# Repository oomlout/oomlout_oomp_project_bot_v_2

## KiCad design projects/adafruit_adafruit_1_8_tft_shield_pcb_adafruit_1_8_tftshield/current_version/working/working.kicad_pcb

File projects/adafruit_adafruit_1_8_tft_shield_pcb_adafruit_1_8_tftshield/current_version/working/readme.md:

# adafruit_1_8_tft_shield_pcb
 
## summary 
* id: adafruit_adafruit_1_8_tft_shield_pcb_adafruit_1_8_tftshield
* user: adafruit
* name: adafruit_1_8_tft_shield_pcb
* board: adafruit_1_8_tftshield
* repo: https://github.com/adafruit/Adafruit-1.8-TFT-Shield-PCB

* src_file_repo_sch: 
* src_file_repo_sch_link: https://github.com/adafruit/Adafruit-1.8-TFT-Shield-PCB/tree/master/
* full details link: https://github.com/oomlout/oomlout_oomp_project_bot_v_2/tree/main/projects/adafruit_adafruit_1_8_tft_shield_pcb_adafruit_1_8_tftshield/current_version/working  

## schematic  
  
[schematic (pdf)](working_schematic.pdf) 

## pcb  

[board (pdf)](working.pdf)  

## working_bom
| Id | Designator | Footprint | Quantity | Designation | Supplier and ref |  | None | 
| --- | --- | --- | --- | --- | --- | --- | --- | 
| 1 | C1,C2 | 0805-NO | 2 | 10uF |  |  | [''] | 
| 2 | DIGITALS1,DIGITALS0 | 1X08_ROUND | 2 |  |  |  | [''] | 
| 3 | Q2 | SOT23-WIDE | 1 | BSS138 |  |  | [''] | 
| 4 | BTN3,RESET0,BTN1,BTN2 | EVQ-Q2_SMALLER | 4 | EVQQ |  |  | [''] | 
| 5 | R9,R2 | 0805-NO | 2 | 10K |  |  | [''] | 
| 6 | U$1 | JD-T1800 | 1 | DISP_LCD_JDT1800 |  |  | [''] | 
| 7 | U$3 | MICROSD | 1 | MICROSD |  |  | [''] | 
| 8 | M1 | ARDUINOR3_ICSP | 1 | ARDUINO_R3_ICSP |  |  | [''] | 
| 9 | U$9 | PCBFEAT-REV-040 | 1 |  |  |  | [''] | 
| 10 | IC1 | QFN24_4MM | 1 | ATSAMD09D14A-MU |  |  | [''] | 
| 11 | JP1 | 1X10_ROUND | 1 |  |  |  | [''] | 
| 12 | IC2 | SOT23-5L | 1 | AP2112K-3.3 |  |  | [''] | 
| 13 | ANALOGS0 | 1X06_ROUND | 1 |  |  |  | [''] | 
| 14 | C3,C4 | 0805-NO | 2 | 0.1uF |  |  | [''] | 
| 15 | R8 | RESPACK_4X0603_NO | 1 | 10K |  |  | [''] | 
| 16 | FID1,FID3 | FIDUCIAL_1MM | 2 | FIDUCIAL_1MM |  |  | [''] | 
| 17 | Q3 | SOT363 | 1 | BSS138 |  |  | [''] | 
| 18 | U1 | TSSOP16 | 1 | 74HC4050 |  |  | [''] | 
| 19 | U$7 | ADAFRUIT_5MM | 1 |  |  |  | [''] | 
| 20 | SW1 | SKQUBAE010 | 1 | NAVSWITCHSKQUABAUE010 |  |  | [''] | 
| 21 | R5 | 0805-NO | 1 | 1K |  |  | [''] | 
| 22 | R1 | 0805-NO | 1 | 22 ohm |  |  | [''] | 
| 23 | AD0,AD1 | SOLDERJUMPER_ARROW_NOPASTE | 2 |  |  |  | [''] | 
| 24 | TP2,TP1 | TESTPOINT_ROUND_2MM | 2 |  |  |  | [''] | 
| 25 | U$5 | ADAFRUIT_TEXT_30MM | 1 |  |  |  | [''] | 
| 26 | U$8 | SEESAW_LOGO | 1 |  |  |  | [''] | 

## bom_schematic
| Ref | Qnty | Value | Cmp name | Footprint | Description | Vendor | DNP | 
| --- | --- | --- | --- | --- | --- | --- | --- | 
| AD0, AD1 | 2 | SOLDERJUMPER | SOLDERJUMPER | working:SOLDERJUMPER_ARROW_NOPASTE |  |  |  | 
| ANALOGS0 | 1 | HEADER-1X6ROUND | HEADER-1X6ROUND | working:1X06_ROUND |  |  |  | 
| BTN1, BTN2, BTN3 | 3 | EVQQ | SWITCH_TACT_SMT_EVQQ2_SMALL | working:EVQ-Q2_SMALLER |  |  |  | 
| C1, C2 | 2 | 10uF | CAP_CERAMIC0805-NOOUTLINE | working:0805-NO |  |  |  | 
| C3, C4 | 2 | 0.1uF | CAP_CERAMIC0805-NOOUTLINE | working:0805-NO |  |  |  | 
| DIGITALS0, DIGITALS1 | 2 | HEADER-1X8ROUND | HEADER-1X8ROUND | working:1X08_ROUND |  |  |  | 
| FID1, FID3 | 2 | FIDUCIAL_1MM | FIDUCIAL_1MM | working:FIDUCIAL_1MM |  |  |  | 
| IC1 | 1 | ATSAMD09D14A-MU | ATSAMD09D14A-MU | working:QFN24_4MM |  |  |  | 
| IC2 | 1 | LP298XS | LP298XS | working:SOT23-5L |  |  |  | 
| JP1 | 1 | HEADER-1X10ROUND | HEADER-1X10ROUND | working:1X10_ROUND |  |  |  | 
| M1 | 1 | ARDUINO_R3_ICSP | ARDUINO_R3_ICSP | working:ARDUINOR3_ICSP |  |  |  | 
| Q2 | 1 | BSS138 | MOSFET-NWIDE | working:SOT23-WIDE |  |  |  | 
| Q3 | 1 | BSS138 | MOSFET-N_DUAL | working:SOT363 |  |  |  | 
| R1 | 1 | 22 ohm | RESISTOR0805_NOOUTLINE | working:0805-NO |  |  |  | 
| R2, R9 | 2 | 10K | RESISTOR0805_NOOUTLINE | working:0805-NO |  |  |  | 
| R5 | 1 | 1K | RESISTOR0805_NOOUTLINE | working:0805-NO |  |  |  | 
| R8 | 1 | 10K | RESISTOR_4PACK_NO | working:RESPACK_4X0603_NO |  |  |  | 
| RESET0 | 1 | EVQQ | SWITCH_TACT_SMT_EVQQ2_SMALL | working:EVQ-Q2_SMALLER |  |  |  | 
| SW1 | 1 | NAVSWITCHSKQUABAUE010 | NAVSWITCHSKQUABAUE010 | working:SKQUBAE010 |  |  |  | 
| TP1, TP2 | 2 | TESTPOINTROUND2MM | TESTPOINTROUND2MM | working:TESTPOINT_ROUND_2MM |  |  |  | 
| U1 | 1 | 74HC4050 | 74HC4050DTSSOP | working:TSSOP16 |  |  |  | 
| U$1 | 1 | DISP_LCD_JDT1800 | DISP_LCD_JDT1800 | working:JD-T1800 |  |  |  | 
| U$3 | 1 | MICROSD | MICROSD | working:MICROSD |  |  |  |

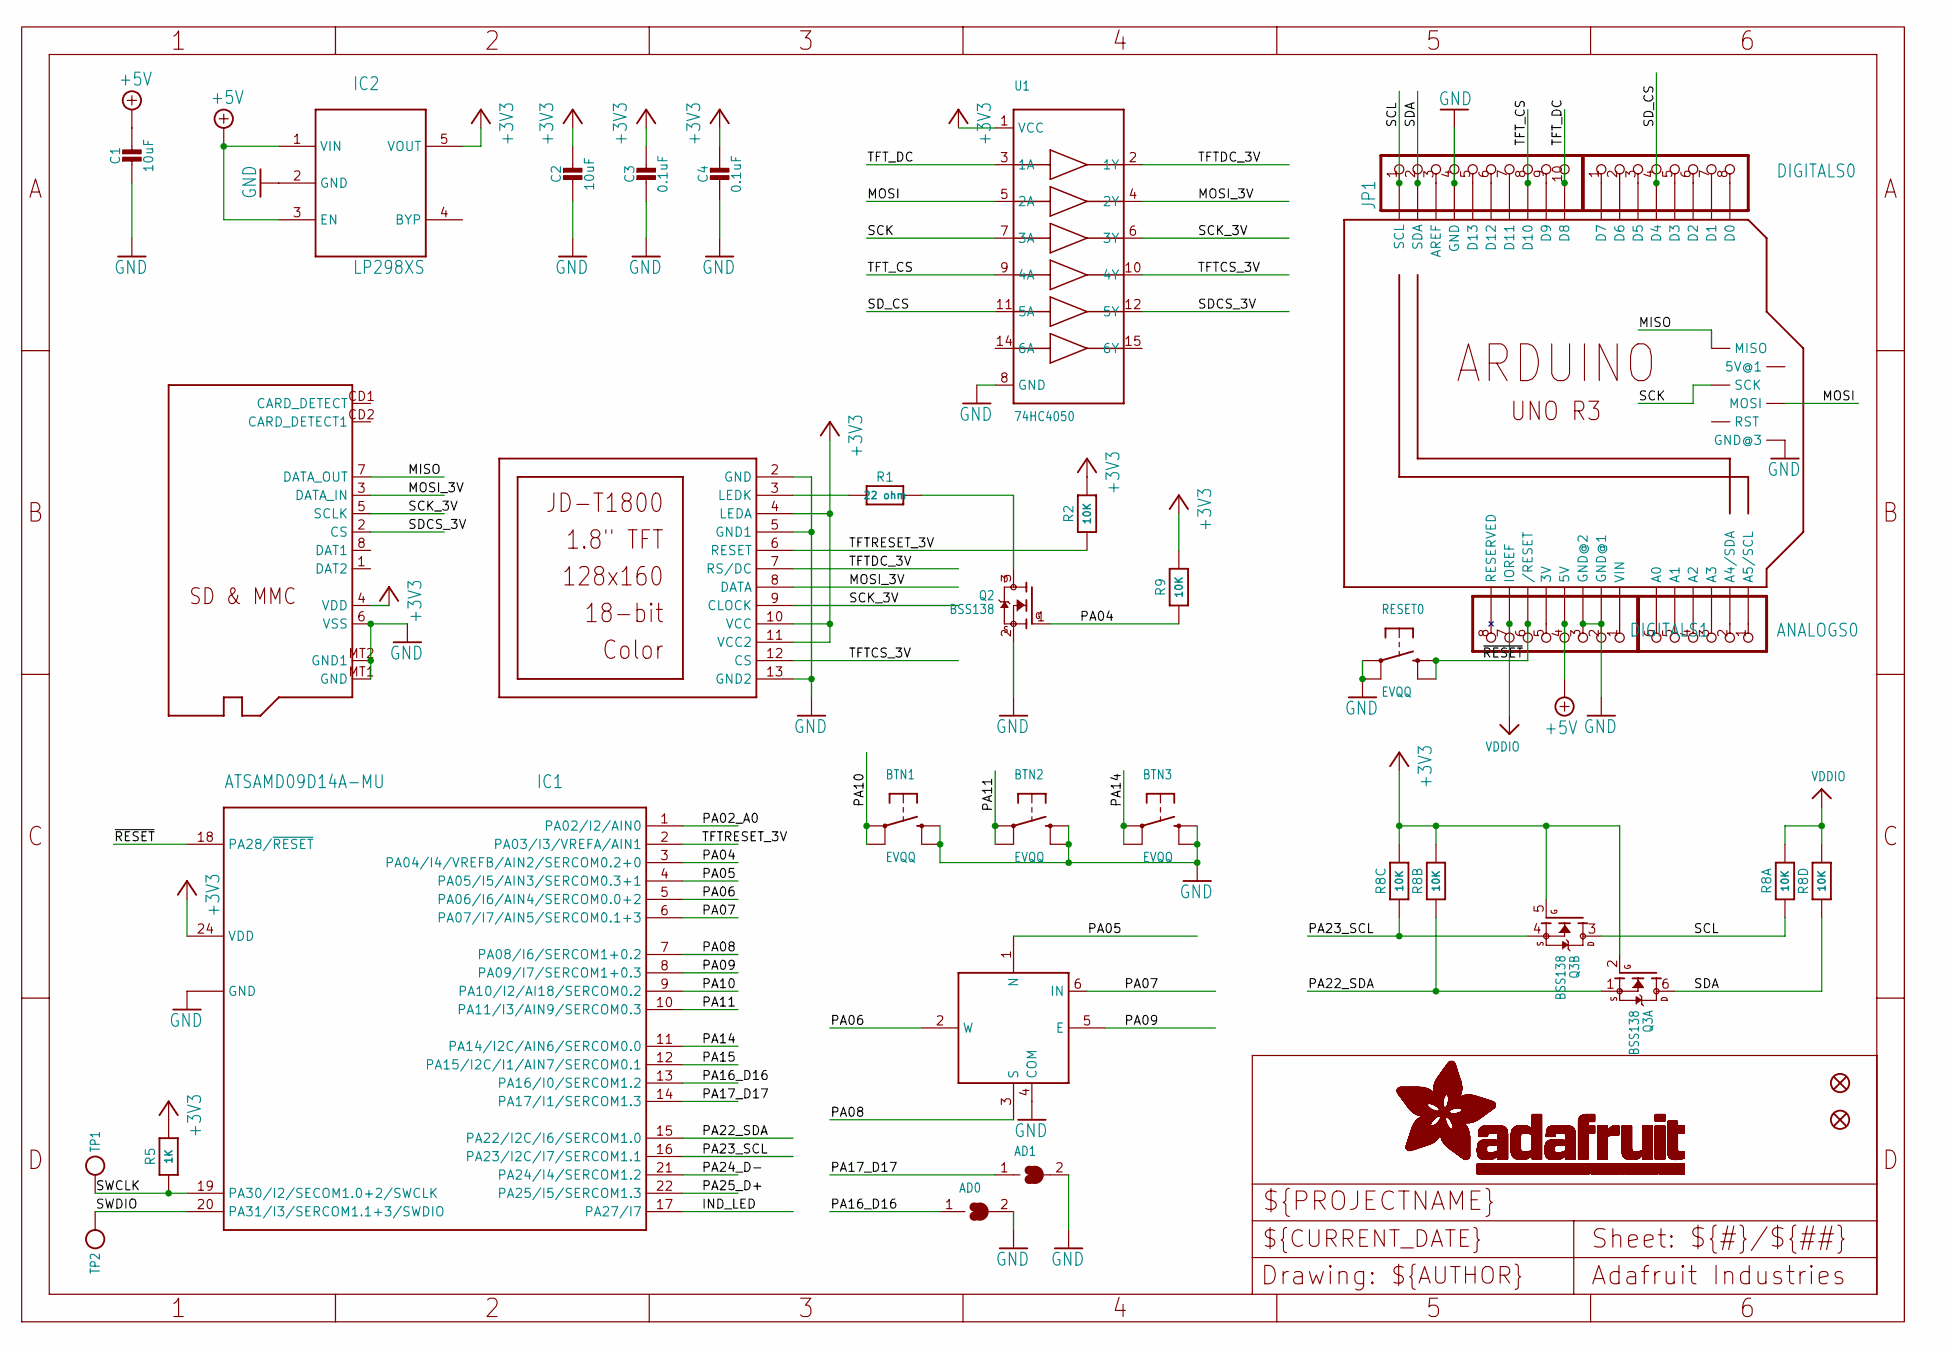
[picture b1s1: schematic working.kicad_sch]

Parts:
AD0, AD1: SOLDERJUMPER; SOLDERJUMPER_ARROW_NOPASTE
ANALOGS0: HEADER-1X6ROUND; 1X06_ROUND
BTN1, BTN2, BTN3: EVQQ; EVQ-Q2_SMALLER
C1, C2: 10uF; 0805-NO
C3, C4: 0.1uF; 0805-NO
DIGITALS0, DIGITALS1: HEADER-1X8ROUND; 1X08_ROUND
FID1, FID3: FIDUCIAL_1MM
IC1: ATSAMD09D14A-MU; QFN24_4MM
IC2: LP298XS; SOT23-5L
JP1: HEADER-1X10ROUND; 1X10_ROUND
M1: ARDUINO_R3_ICSP; ARDUINOR3_ICSP
Q2: BSS138; SOT23-WIDE
Q3: BSS138; SOT363
R1: 22 ohm; 0805-NO
R2, R9: 10K; 0805-NO
R5: 1K; 0805-NO
R8: 10K; RESPACK_4X0603_NO
RESET0: EVQQ; EVQ-Q2_SMALLER
SW1: NAVSWITCHSKQUABAUE010; SKQUBAE010
TP1, TP2: TESTPOINTROUND2MM; TESTPOINT_ROUND_2MM
U1: 74HC4050; TSSOP16
U$1: DISP_LCD_JDT1800; JD-T1800
U$3: MICROSD

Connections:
+3.3V: DIGITALS1.5, M1.3V
+3V3: C2.1, C3.1, C4.1, IC1.24 (VDD), IC2.5 (VOUT), Q3.2 (G), Q3.5 (G), R2.2, R5.2, R8.6 (2), R8.7 (2), R9.2, U1.1 (VCC), U$1.4 (LEDA), U$1.10 (VCC), U$1.11 (VCC2), U$3.4 (VDD)
+5V: C1.1, DIGITALS1.4, IC2.1 (VIN), IC2.3 (EN), M1.5V
A0: ANALOGS0.6, M1.A0
A1: ANALOGS0.5, M1.A1
A2: ANALOGS0.4, M1.A2
A4: ANALOGS0.2, M1.A4 (A4/SDA)
A5: ANALOGS0.1, M1.A5 (A5/SCL)
AREF: JP1.3, M1.AREF
D0: DIGITALS0.8, M1.D0
D1: DIGITALS0.7, M1.D1
D2: DIGITALS0.6, M1.D2
D3: DIGITALS0.5, M1.D3
D5: DIGITALS0.3, M1.D5
D6: DIGITALS0.2, M1.D6
D7: DIGITALS0.1, M1.D7
D9: JP1.9, M1.D9
GND: AD0.2, AD1.2, BTN1.B (S), BTN1.B' (S1), BTN2.B (S), BTN2.B' (S1), BTN3.B (S), BTN3.B' (S1), C1.2, C2.2, C3.2, C4.2, DIGITALS1.2, DIGITALS1.3, IC1.23 (GND), IC1.THERM (GND), IC2.2 (GND), JP1.4, M1.GND, M1.GND@1 (GND@2), M1.GND@2 (GND@3), M1.GND@3 (GND@1), Q2.2 (S), RESET0.A, RESET0.A' (P1), SW1.4 (COM), U1.8 (GND), U$1.2 (GND), U$1.5 (GND1), U$1.13 (GND2), U$3.6 (VSS), U$3.MT1 (GND), U$3.MT2 (GND1)
IND_LED: IC1.17 (PA27/I7)
MISO: M1.MISO, U$3.7 (DATA_OUT)
MOSI: M1.MOSI, U1.5 (2A)
MOSI_3V: U1.4 (2Y), U$1.8 (DATA), U$3.3 (DATA_IN)
unnamed: R1.1, U$1.3 (LEDK)
unnamed: Q2.3 (D), R1.2
unnamed: JP1.5, M1.D13
unnamed: JP1.6, M1.D12
unnamed: JP1.7, M1.D11
unnamed: ANALOGS0.3, M1.A3
unnamed: DIGITALS1.8, M1.RESERVED
PA02_A0: IC1.1 (PA02/I2/AIN0)
PA04: IC1.3 (PA04/I4/VREFB/AIN2/SERCOM0.2+0), Q2.1 (G), R9.1
PA05: IC1.4 (PA05/I5/AIN3/SERCOM0.3+1), SW1.1 (N)
PA06: IC1.5 (PA06/I6/AIN4/SERCOM0.0+2), SW1.2 (W)
PA07: IC1.6 (PA07/I7/AIN5/SERCOM0.1+3), SW1.6 (IN)
PA08: IC1.7 (PA08/I6/SERCOM1+0.2), SW1.3 (S)
PA09: IC1.8 (PA09/I7/SERCOM1+0.3), SW1.5 (E)
PA10: BTN1.A, BTN1.A' (P1), IC1.9 (PA10/I2/AI18/SERCOM0.2)
PA11: BTN2.A, BTN2.A' (P1), IC1.10 (PA11/I3/AIN9/SERCOM0.3)
PA14: BTN3.A, BTN3.A' (P1), IC1.11 (PA14/I2C/AIN6/SERCOM0.0)
PA15: IC1.12 (PA15/I2C/I1/AIN7/SERCOM0.1)
PA16_D16: AD0.1, IC1.13 (PA16/I0/SERCOM1.2)
PA17_D17: AD1.1, IC1.14 (PA17/I1/SERCOM1.3)
PA22_SDA: IC1.15 (PA22/I2C/I6/SERCOM1.0), Q3.1 (S), R8.2 (1)
PA23_SCL: IC1.16 (PA23/I2C/I7/SERCOM1.1), Q3.4 (S), R8.3 (1)
PA24_D-: IC1.21 (PA24/I4/SERCOM1.2)
PA25_D+: IC1.22 (PA25/I5/SERCOM1.3)
SCK: M1.SCK, U1.7 (3A)
SCK_3V: U1.6 (3Y), U$1.9 (CLOCK), U$3.5 (SCLK)
SCL: JP1.1, M1.SCL, Q3.3 (D), R8.1
SDA: JP1.2, M1.SDA, Q3.6 (D), R8.4 (1)
SDCS_3V: U1.12 (5Y), U$3.2 (CS)
SD_CS: DIGITALS0.4, M1.D4, U1.11 (5A)
SWCLK: IC1.19 (PA30/I2/SECOM1.0+2/SWCLK), R5.1, TP1.P$1
SWDIO: IC1.20 (PA31/I3/SERCOM1.1+3/SWDIO), TP2.P$1
TFTCS_3V: U1.10 (4Y), U$1.12 (CS)
TFTDC_3V: U1.2 (1Y), U$1.7 (RS/DC)
TFTRESET_3V: IC1.2 (PA03/I3/VREFA/AIN1), R2.1, U$1.6 (RESET)
TFT_CS: JP1.8, M1.D10, U1.9 (4A)
TFT_DC: JP1.10, M1.D8, U1.3 (1A)
VDDIO: DIGITALS1.7, M1.IOREF, R8.5 (2), R8.8 (2)
VIN: DIGITALS1.1, M1.VIN
~RESET: DIGITALS1.6, IC1.18 (PA28/~RESET), M1.RESET (/RESET), RESET0.B (S), RESET0.B' (S1)

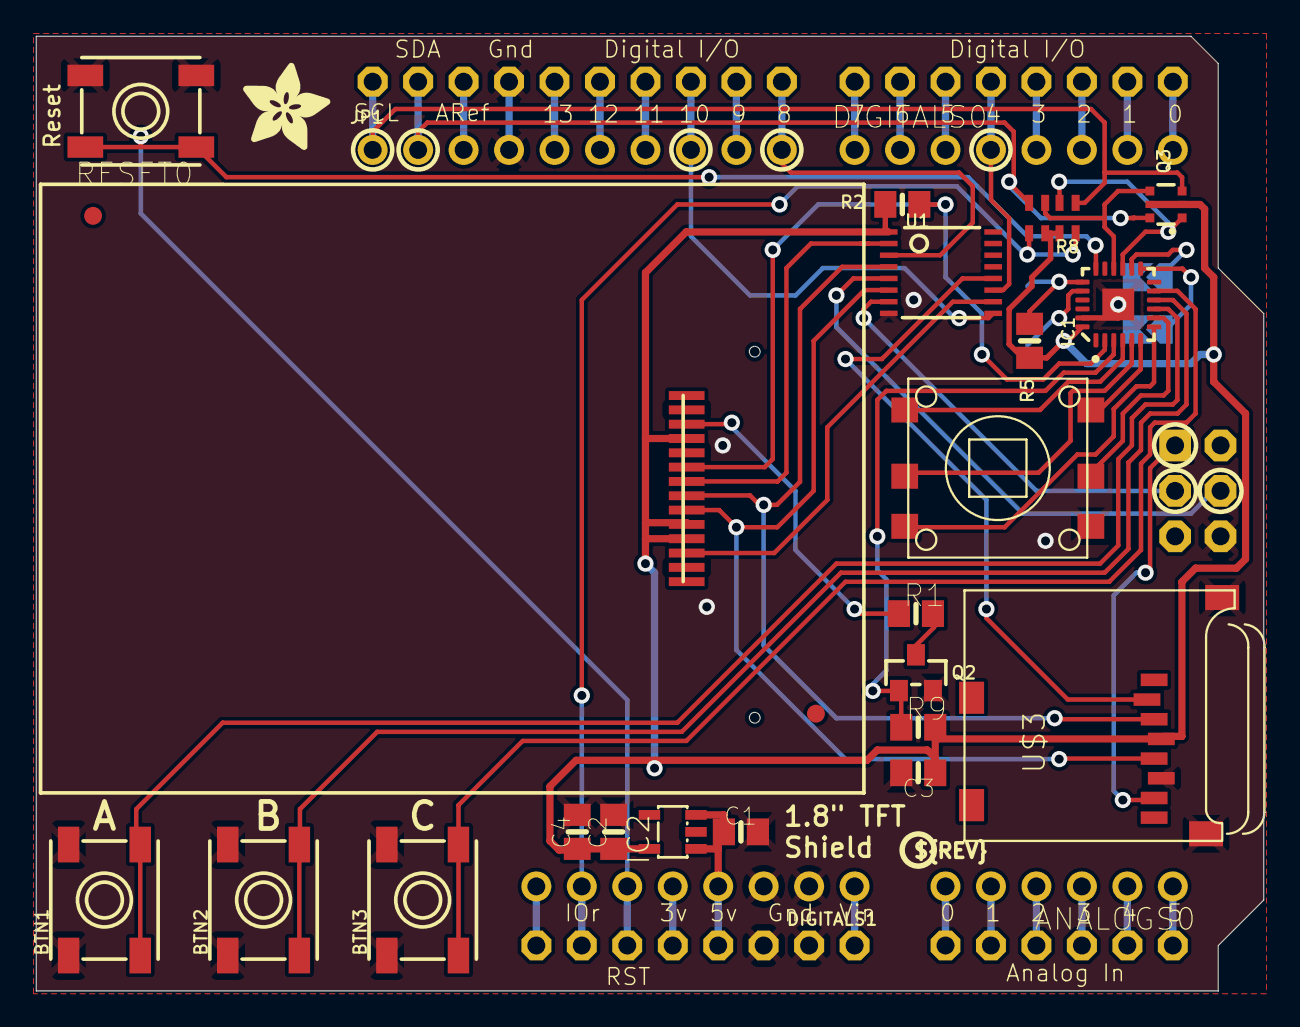
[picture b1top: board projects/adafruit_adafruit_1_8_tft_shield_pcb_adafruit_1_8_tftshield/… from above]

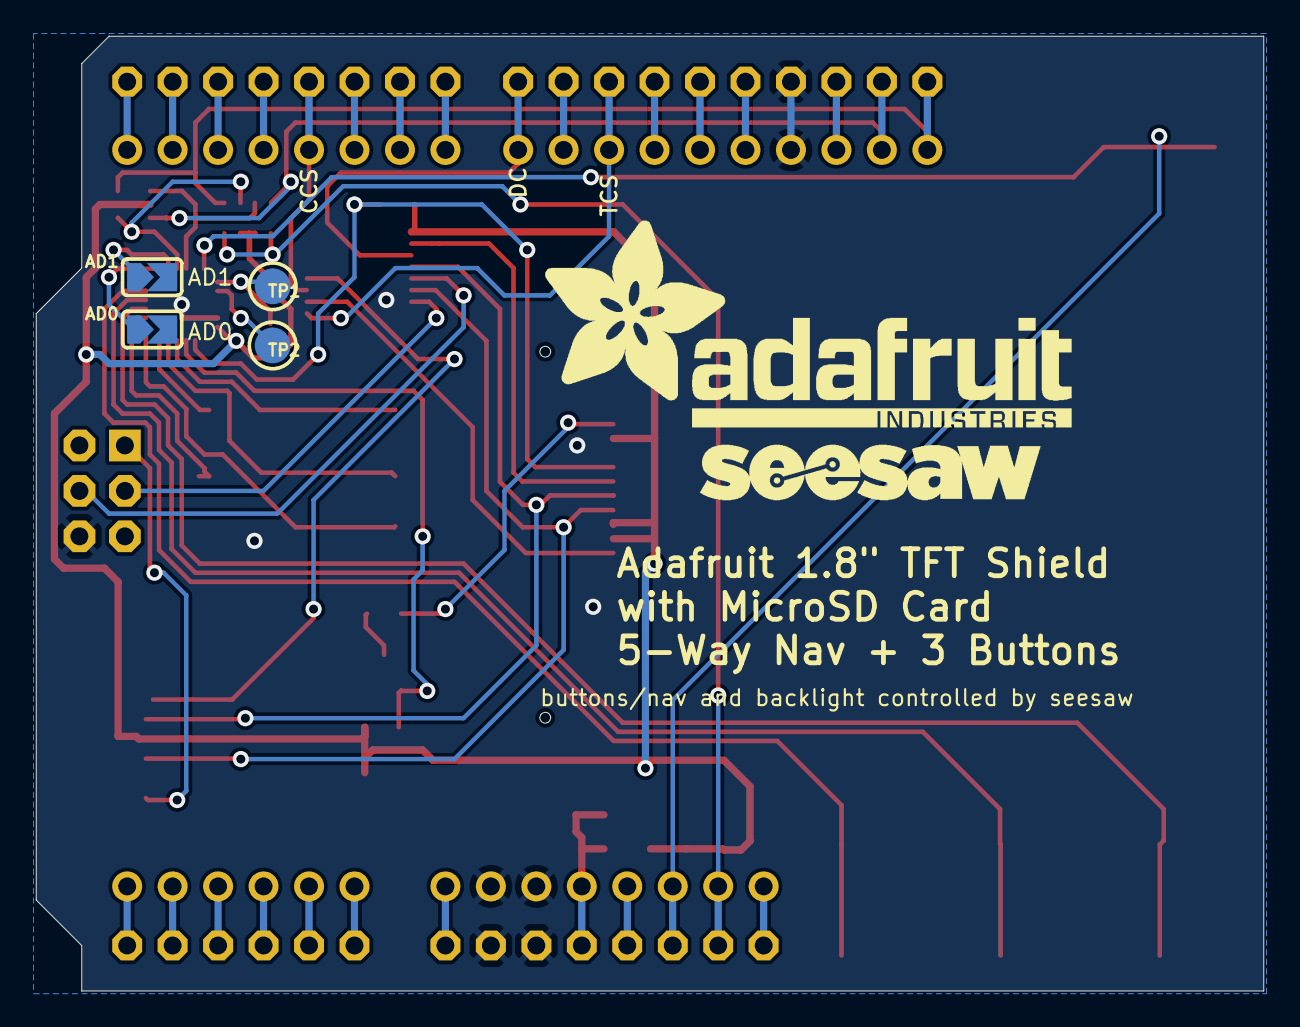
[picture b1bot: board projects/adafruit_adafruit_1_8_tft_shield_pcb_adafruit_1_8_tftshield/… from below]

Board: 16 copper layers, 68.6 x 53.3 mm, 36 parts (6 on the bottom side), 57 nets.

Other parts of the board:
U$5: ADAFRUIT_TEXT_30MM
U$7: ADAFRUIT_5MM
U$8: SEESAW_LOGO
U$9: PCBFEAT-REV-040

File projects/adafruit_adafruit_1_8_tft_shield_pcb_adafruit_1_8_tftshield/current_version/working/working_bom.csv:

"Id";"Designator";"Footprint";"Quantity";"Designation";"Supplier and ref";
1;"C1,C2";"0805-NO";2;"10uF";;;
2;"DIGITALS1,DIGITALS0";"1X08_ROUND";2;"";;;
3;"Q2";"SOT23-WIDE";1;"BSS138";;;
4;"BTN3,RESET0,BTN1,BTN2";"EVQ-Q2_SMALLER";4;"EVQQ";;;
5;"R9,R2";"0805-NO";2;"10K";;;
6;"U$1";"JD-T1800";1;"DISP_LCD_JDT1800";;;
7;"U$3";"MICROSD";1;"MICROSD";;;
8;"M1";"ARDUINOR3_ICSP";1;"ARDUINO_R3_ICSP";;;
9;"U$9";"PCBFEAT-REV-040";1;"";;;
10;"IC1";"QFN24_4MM";1;"ATSAMD09D14A-MU";;;
11;"JP1";"1X10_ROUND";1;"";;;
12;"IC2";"SOT23-5L";1;"AP2112K-3.3";;;
13;"ANALOGS0";"1X06_ROUND";1;"";;;
14;"C3,C4";"0805-NO";2;"0.1uF";;;
15;"R8";"RESPACK_4X0603_NO";1;"10K";;;
16;"FID1,FID3";"FIDUCIAL_1MM";2;"FIDUCIAL_1MM";;;
17;"Q3";"SOT363";1;"BSS138";;;
18;"U1";"TSSOP16";1;"74HC4050";;;
19;"U$7";"ADAFRUIT_5MM";1;"";;;
20;"SW1";"SKQUBAE010";1;"NAVSWITCHSKQUABAUE010";;;
21;"R5";"0805-NO";1;"1K";;;
22;"R1";"0805-NO";1;"22 ohm";;;
23;"AD0,AD1";"SOLDERJUMPER_ARROW_NOPASTE";2;"";;;
24;"TP2,TP1";"TESTPOINT_ROUND_2MM";2;"";;;
25;"U$5";"ADAFRUIT_TEXT_30MM";1;"";;;
26;"U$8";"SEESAW_LOGO";1;"";;;

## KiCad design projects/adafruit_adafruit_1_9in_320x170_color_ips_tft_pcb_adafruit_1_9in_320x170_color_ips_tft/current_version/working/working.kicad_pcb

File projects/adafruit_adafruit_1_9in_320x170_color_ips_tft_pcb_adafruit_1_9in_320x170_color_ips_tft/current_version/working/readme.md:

# adafruit_1_9in_320x170_color_ips_tft_pcb
 
## summary 
* id: adafruit_adafruit_1_9in_320x170_color_ips_tft_pcb_adafruit_1_9in_320x170_color_ips_tft
* user: adafruit
* name: adafruit_1_9in_320x170_color_ips_tft_pcb
* board: adafruit_1_9in_320x170_color_ips_tft
* repo: https://github.com/adafruit/Adafruit-1.9in-320x170-Color-IPS-TFT-PCB

* src_file_repo_sch: 
* src_file_repo_sch_link: https://github.com/adafruit/Adafruit-1.9in-320x170-Color-IPS-TFT-PCB/tree/main/
* full details link: https://github.com/oomlout/oomlout_oomp_project_bot_v_2/tree/main/projects/adafruit_adafruit_1_9in_320x170_color_ips_tft_pcb_adafruit_1_9in_320x170_color_ips_tft/current_version/working  

## schematic  
  
[schematic (pdf)](working_schematic.pdf) 

## pcb  

[board (pdf)](working.pdf)  

## working_bom
| Id | Designator | Footprint | Quantity | Designation | Supplier and ref |  | None | 
| --- | --- | --- | --- | --- | --- | --- | --- | 
| 1 | U$2 | PCBFEAT-REV-040 | 1 |  |  |  | [''] | 
| 2 | C5,C4,C1,C2 | 0805-NO | 4 | 10uF |  |  | [''] | 
| 3 | TFT1 | TFT_1.9IN_170X320_30P | 1 | DISP_LCD_ST7789_1.9IN |  |  | [''] | 
| 4 | IC4 | SOT23 | 1 | APX803-SAG |  |  | [''] | 
| 5 | IC2 | SOT23-5L | 1 | AP2112 |  |  | [''] | 
| 6 | R1 | RESPACK_4X0603 | 1 | 10k |  |  | [''] | 
| 7 | Q3 | SOT23-WIDE | 1 | BSS138 |  |  | [''] | 
| 8 | U1 | TSSOP16 | 1 | 74HC4050PWR |  |  | [''] | 
| 9 | JP1 | 1X11_ROUND_76 | 1 |  |  |  | [''] | 
| 10 | R6 | RESPACK_4X0603 | 1 | ~22 OHM |  |  | [''] | 
| 11 | U$4,U$5 | FIDUCIAL_1MM | 2 | FIDUCIAL_1MM |  |  | [''] | 
| 12 | X1 | EYE_SPI_DISPLAY_BOTCONTACT | 1 | EYE_SPI_DISPLAY_FLIP |  |  | [''] | 
| 13 | C3 | 0603-NO | 1 | 0.1uF |  |  | [''] | 
| 14 | U$22 | EYESPI_MINI_LOGO | 1 |  |  |  | [''] | 
| 15 | Q2 | MICROSD | 1 | MICROSD |  |  | [''] | 
| 16 | U$21 | ADAFRUIT_3.5MM | 1 |  |  |  | [''] | 
| 17 | U$10,U$9,U$8,U$7 | MOUNTINGHOLE_2.5_PLATED | 4 | MOUNTINGHOLE2.5 |  |  | [''] | 

## bom_schematic
| Ref | Qnty | Value | Cmp name | Footprint | Description | Vendor | DNP | 
| --- | --- | --- | --- | --- | --- | --- | --- | 
| C1, C2, C4, C5 | 4 | 10uF | CAP_CERAMIC0805-NOOUTLINE | working:0805-NO |  |  |  | 
| C3 | 1 | 0.1uF | CAP_CERAMIC0603_NO | working:0603-NO |  |  |  | 
| IC2 | 1 | LP298XS | LP298XS | working:SOT23-5L |  |  |  | 
| IC4 | 1 | APX803-SAG | AXP083-SAG | working:SOT23 |  |  |  | 
| JP1 | 1 | HEADER-1X1176MIL | HEADER-1X1176MIL | working:1X11_ROUND_76 |  |  |  | 
| Q2 | 1 | MICROSD | MICROSD | working:MICROSD |  |  |  | 
| Q3 | 1 | BSS138 | MOSFET-NWIDE | working:SOT23-WIDE |  |  |  | 
| R1 | 1 | 10k | RESISTOR_4PACK | working:RESPACK_4X0603 |  |  |  | 
| R6 | 1 | ~22 OHM | RESISTOR_4PACK | working:RESPACK_4X0603 |  |  |  | 
| TFT1 | 1 | DISP_LCD_ST7789_1.9IN | DISP_LCD_ST7789_1.9IN | working:TFT_1.9IN_170X320_30P |  |  |  | 
| U1 | 1 | 74HC4050PWR | 74HC4050DTSSOP | working:TSSOP16 |  |  |  | 
| U$4, U$5 | 2 | FIDUCIAL_1MM | FIDUCIAL_1MM | working:FIDUCIAL_1MM |  |  |  | 
| U$7, U$8, U$9, U$10 | 4 | MOUNTINGHOLE2.5 | MOUNTINGHOLE2.5 | working:MOUNTINGHOLE_2.5_PLATED |  |  |  | 
| X1 | 1 | EYE_SPI_DISPLAY_FLIP | EYE_SPI_DISPLAY_FLIP | working:EYE_SPI_DISPLAY_BOTCONTACT |  |  |  |

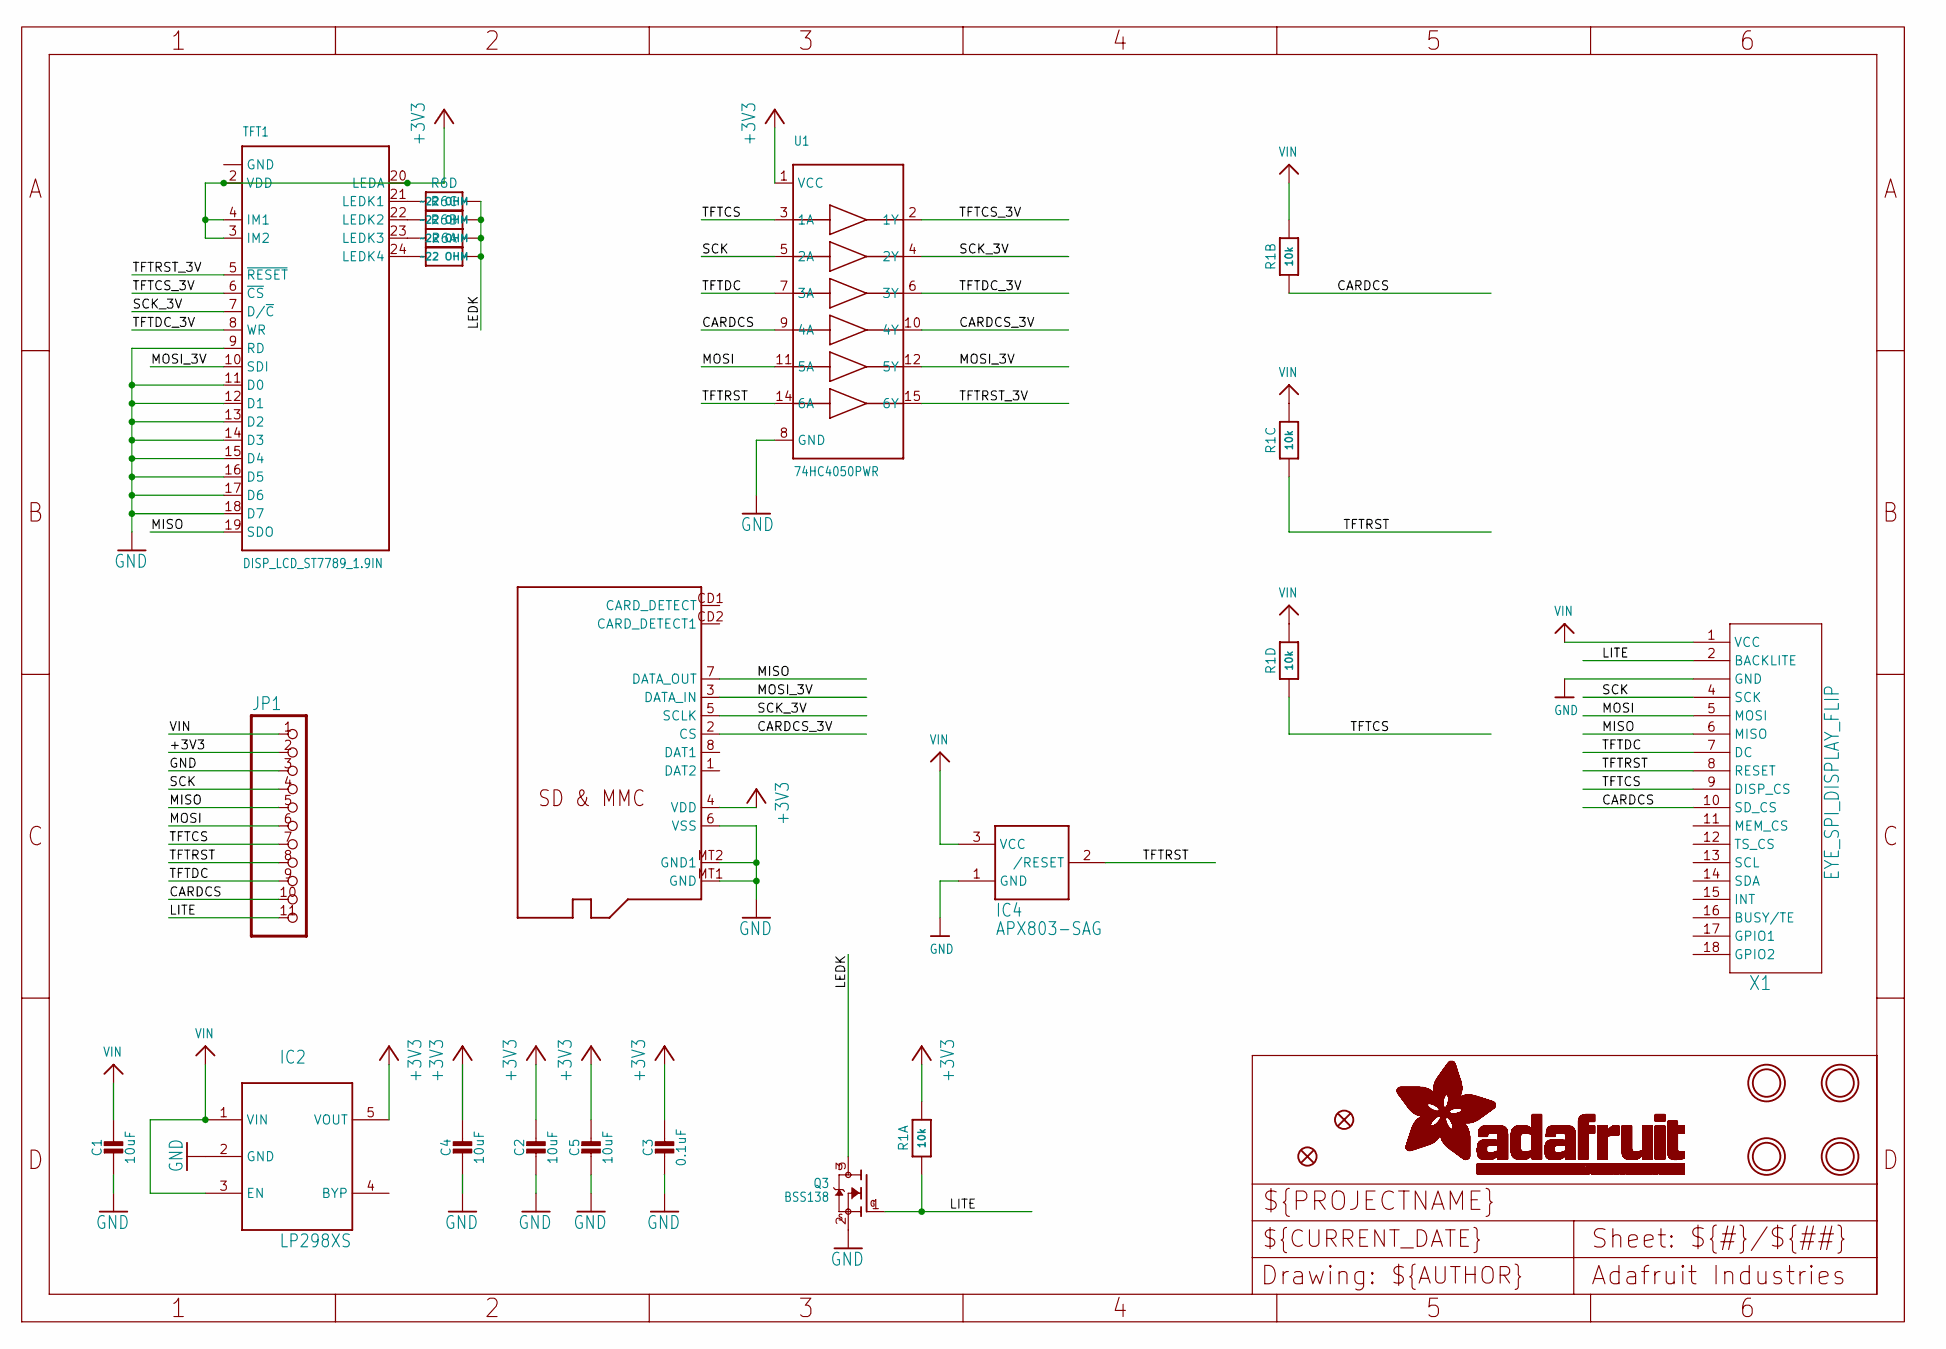
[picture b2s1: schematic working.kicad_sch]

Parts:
C1, C2, C4, C5: 10uF; 0805-NO
C3: 0.1uF; 0603-NO
IC2: LP298XS; SOT23-5L
IC4: APX803-SAG; SOT23
JP1: HEADER-1X1176MIL; 1X11_ROUND_76
Q2: MICROSD
Q3: BSS138; SOT23-WIDE
R1: 10k; RESPACK_4X0603
R6: ~22 OHM; RESPACK_4X0603
TFT1: DISP_LCD_ST7789_1.9IN; TFT_1.9IN_170X320_30P
U1: 74HC4050PWR; TSSOP16
U$4, U$5: FIDUCIAL_1MM
U$7, U$8, U$9, U$10: MOUNTINGHOLE2.5; MOUNTINGHOLE_2.5_PLATED
X1: EYE_SPI_DISPLAY_FLIP; EYE_SPI_DISPLAY_BOTCONTACT

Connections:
+3V3: C2.1, C3.1, C4.1, C5.1, IC2.5 (VOUT), JP1.2, Q2.4 (VDD), R1.8 (2), TFT1.2 (VDD), TFT1.3 (IM2), TFT1.4 (IM1), TFT1.20 (LEDA), U1.1 (VCC)
CARDCS: JP1.10, R1.2 (1), U1.9 (4A), X1.10 (SD_CS)
CARDCS_3V: Q2.2 (CS), U1.10 (4Y)
LEDK: Q3.3 (D), R6.5 (2), R6.6 (2), R6.7 (2), R6.8 (2)
LITE: JP1.11, Q3.1 (G), R1.1, X1.2 (BACKLITE)
MISO: JP1.5, Q2.7 (DATA_OUT), TFT1.19 (SDO), X1.6 (MISO)
MOSI: JP1.6, U1.11 (5A), X1.5 (MOSI)
MOSI_3V: Q2.3 (DATA_IN), TFT1.10 (SDI), U1.12 (5Y)
unnamed: R6.4 (1), TFT1.21 (LEDK1)
unnamed: R6.3 (1), TFT1.22 (LEDK2)
unnamed: R6.2 (1), TFT1.23 (LEDK3)
unnamed: R6.1, TFT1.24 (LEDK4)
SCK: JP1.4, U1.5 (2A), X1.4 (SCK)
SCK_3V: Q2.5 (SCLK), TFT1.7 (D/~C), U1.4 (2Y)
TFTCS: JP1.7, R1.4 (1), U1.3 (1A), X1.9 (DISP_CS)
TFTCS_3V: TFT1.6 (~CS), U1.2 (1Y)
TFTDC: JP1.9, U1.7 (3A), X1.7 (DC)
TFTDC_3V: TFT1.8 (WR), U1.6 (3Y)
TFTRST: IC4.2 (/RESET), JP1.8, R1.3 (1), U1.14 (6A), X1.8 (RESET)
TFTRST_3V: TFT1.5 (~RESET), U1.15 (6Y)
VIN: C1.1, IC2.1 (VIN), IC2.3 (EN), IC4.3 (VCC), JP1.1, R1.5 (2), R1.6 (2), R1.7 (2), X1.1 (VCC)

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
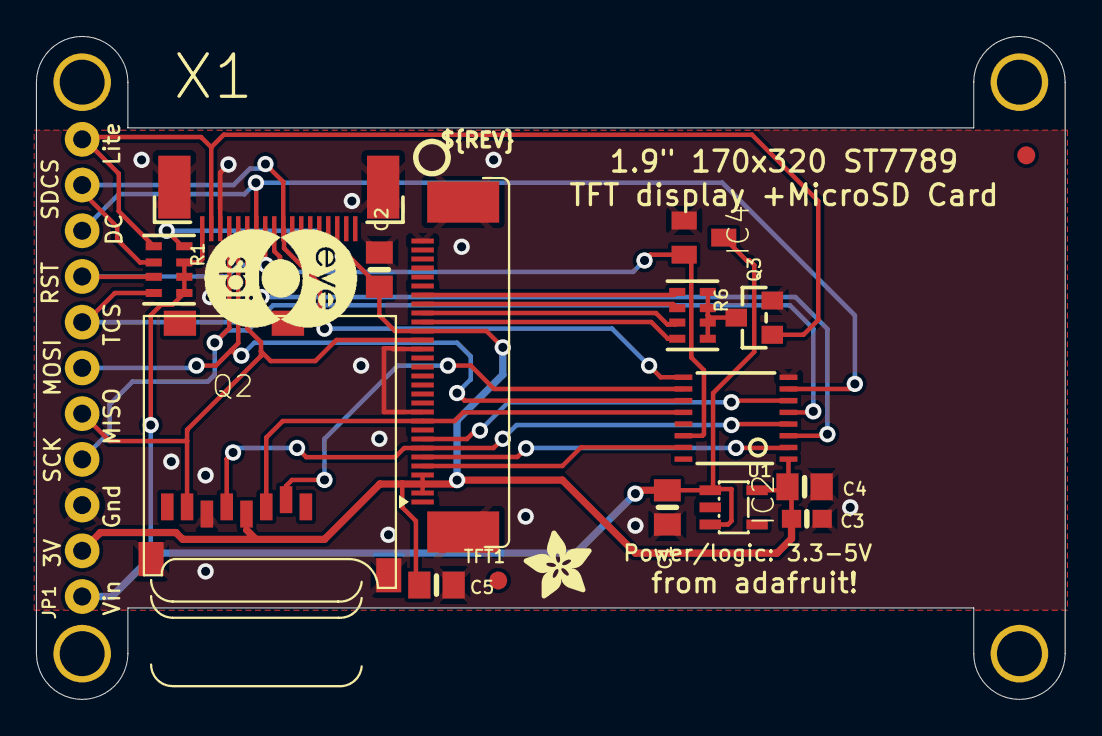
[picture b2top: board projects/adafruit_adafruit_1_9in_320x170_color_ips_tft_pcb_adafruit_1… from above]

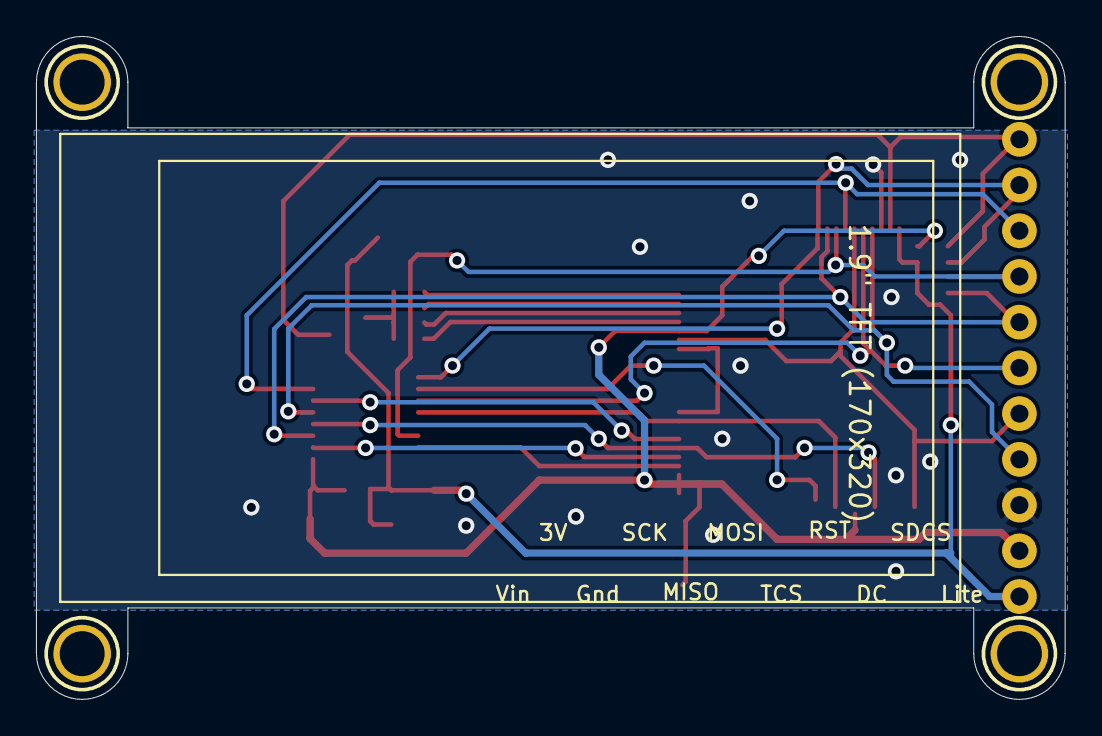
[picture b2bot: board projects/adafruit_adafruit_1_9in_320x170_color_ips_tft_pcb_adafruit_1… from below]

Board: 16 copper layers, 57.1 x 36.8 mm, 24 parts (4 on the bottom side), 22 nets.

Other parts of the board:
U$2: PCBFEAT-REV-040
U$21: ADAFRUIT_3.5MM
U$22: EYESPI_MINI_LOGO

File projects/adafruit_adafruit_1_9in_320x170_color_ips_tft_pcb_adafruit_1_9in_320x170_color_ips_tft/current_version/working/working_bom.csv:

"Id";"Designator";"Footprint";"Quantity";"Designation";"Supplier and ref";
1;"U$2";"PCBFEAT-REV-040";1;"";;;
2;"C5,C4,C1,C2";"0805-NO";4;"10uF";;;
3;"TFT1";"TFT_1.9IN_170X320_30P";1;"DISP_LCD_ST7789_1.9IN";;;
4;"IC4";"SOT23";1;"APX803-SAG";;;
5;"IC2";"SOT23-5L";1;"AP2112";;;
6;"R1";"RESPACK_4X0603";1;"10k";;;
7;"Q3";"SOT23-WIDE";1;"BSS138";;;
8;"U1";"TSSOP16";1;"74HC4050PWR";;;
9;"JP1";"1X11_ROUND_76";1;"";;;
10;"R6";"RESPACK_4X0603";1;"~22 OHM";;;
11;"U$4,U$5";"FIDUCIAL_1MM";2;"FIDUCIAL_1MM";;;
12;"X1";"EYE_SPI_DISPLAY_BOTCONTACT";1;"EYE_SPI_DISPLAY_FLIP";;;
13;"C3";"0603-NO";1;"0.1uF";;;
14;"U$22";"EYESPI_MINI_LOGO";1;"";;;
15;"Q2";"MICROSD";1;"MICROSD";;;
16;"U$21";"ADAFRUIT_3.5MM";1;"";;;
17;"U$10,U$9,U$8,U$7";"MOUNTINGHOLE_2.5_PLATED";4;"MOUNTINGHOLE2.5";;;

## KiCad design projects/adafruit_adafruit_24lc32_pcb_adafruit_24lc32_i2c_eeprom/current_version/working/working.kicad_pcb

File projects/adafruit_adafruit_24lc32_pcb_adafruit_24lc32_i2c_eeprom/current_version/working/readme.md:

# adafruit_24lc32_pcb
 
## summary 
* id: adafruit_adafruit_24lc32_pcb_adafruit_24lc32_i2c_eeprom
* user: adafruit
* name: adafruit_24lc32_pcb
* board: adafruit_24lc32_i2c_eeprom
* repo: https://github.com/adafruit/Adafruit-24LC32-PCB

* src_file_repo_sch: 
* src_file_repo_sch_link: https://github.com/adafruit/Adafruit-24LC32-PCB/tree/main/
* full details link: https://github.com/oomlout/oomlout_oomp_project_bot_v_2/tree/main/projects/adafruit_adafruit_24lc32_pcb_adafruit_24lc32_i2c_eeprom/current_version/working  

## schematic  
  
[schematic (pdf)](working_schematic.pdf) 

## pcb  

[board (pdf)](working.pdf)  

## working_bom
| Id | Designator | Footprint | Quantity | Designation | Supplier and ref |  | None | 
| --- | --- | --- | --- | --- | --- | --- | --- | 
| 1 | JP3 | 1X04_ROUND | 1 |  |  |  | [''] | 
| 2 | U1 | SOIC8_150MIL | 1 | Generic I2C EEPROM |  |  | [''] | 
| 3 | R1,R3 | RESPACK_4X0603 | 2 | 10K |  |  | [''] | 
| 4 | U$32 | ADAFRUIT_3.5MM | 1 |  |  |  | [''] | 
| 5 | U$17,U$19,U$1,U$21 | MOUNTINGHOLE_2.5_PLATED | 4 | MOUNTINGHOLE2.5 |  |  | [''] | 
| 6 | Q2 | SOT363 | 1 | BSS138 |  |  | [''] | 
| 7 | C1 | 0603-NO | 1 | 0.1uF |  |  | [''] | 
| 8 | CONN4,CONN3 | JST_SH4 | 2 | STEMMA_I2C_QT |  |  | [''] | 
| 9 | U3 | USON8 | 1 | Generic I2C EEPROM |  |  | [''] | 
| 10 | C3,C2 | 0805-NO | 2 | 10uF |  |  | [''] | 
| 11 | JP1 | 1X06_ROUND_70 | 1 |  |  |  | [''] | 
| 12 | D1 | CHIPLED_0603_NOOUTLINE | 1 | GREEN |  |  | [''] | 
| 13 | U2 | SOT23-5 | 1 | AP2112K-3.3 |  |  | [''] | 
| 14 | FID4,FID3 | FIDUCIAL_1MM | 2 | FIDUCIAL_1MM |  |  | [''] | 
| 15 | U$25 | PCBFEAT-REV-040 | 1 |  |  |  | [''] | 
| 16 | U$31,U$30 | STEMMAQT | 2 |  |  |  | [''] | 
| 17 | SJ2,SJ1,SJ3 | SOLDERJUMPER_ARROW_NOPASTE | 3 |  |  |  | [''] | 

## bom_schematic
| Ref | Qnty | Value | Cmp name | Footprint | Description | Vendor | DNP | 
| --- | --- | --- | --- | --- | --- | --- | --- | 
| C1 | 1 | 0.1uF | CAP_CERAMIC0603_NO | working:0603-NO |  |  |  | 
| C2, C3 | 2 | 10uF | CAP_CERAMIC0805-NOOUTLINE | working:0805-NO |  |  |  | 
| CONN3, CONN4 | 2 | STEMMA_I2C_QT | STEMMA_I2C_QT | working:JST_SH4 |  |  |  | 
| D1 | 1 | GREEN | LED0603_NOOUTLINE | working:CHIPLED_0603_NOOUTLINE |  |  |  | 
| FID3, FID4 | 2 | FIDUCIAL_1MM | FIDUCIAL_1MM | working:FIDUCIAL_1MM |  |  |  | 
| JP1 | 1 | HEADER-1X670MIL | HEADER-1X670MIL | working:1X06_ROUND_70 |  |  |  | 
| JP3 | 1 | HEADER-1X4ROUND | HEADER-1X4ROUND | working:1X04_ROUND |  |  |  | 
| Q2 | 1 | BSS138 | MOSFET-N_DUAL | working:SOT363 |  |  |  | 
| R1, R3 | 2 | 10K | RESISTOR_4PACK | working:RESPACK_4X0603 |  |  |  | 
| SJ1, SJ2, SJ3 | 3 | SOLDERJUMPER | SOLDERJUMPER | working:SOLDERJUMPER_ARROW_NOPASTE |  |  |  | 
| U1 | 1 | Generic I2C EEPROM | EEPROM_I2C_8PIN_GENERIC | working:SOIC8_150MIL |  |  |  | 
| U2 | 1 | AP2112K-3.3 | VREG_SOT23-5 | working:SOT23-5 |  |  |  | 
| U3 | 1 | Generic I2C EEPROM | EEPROM_I2C_8PIN_GENERIC_SON8 | working:USON8 |  |  |  | 
| U$1, U$17, U$19, U$21 | 4 | MOUNTINGHOLE2.5 | MOUNTINGHOLE2.5 | working:MOUNTINGHOLE_2.5_PLATED |  |  |  | 

## mounting_holes
| x | y | package | value | ref | size | 
| --- | --- | --- | --- | --- | --- | 
| 0.0 | 12.7 | MOUNTINGHOLE_2.5_PLATED | MOUNTINGHOLE2.5 | U$1 | m3 | 
| 20.32 | 12.7 | MOUNTINGHOLE_2.5_PLATED | MOUNTINGHOLE2.5 | U$17 | m3 | 
| 0.0 | 0.0 | MOUNTINGHOLE_2.5_PLATED | MOUNTINGHOLE2.5 | U$19 | m3 | 
| 20.32 | 0.0 | MOUNTINGHOLE_2.5_PLATED | MOUNTINGHOLE2.5 | U$21 | m3 |

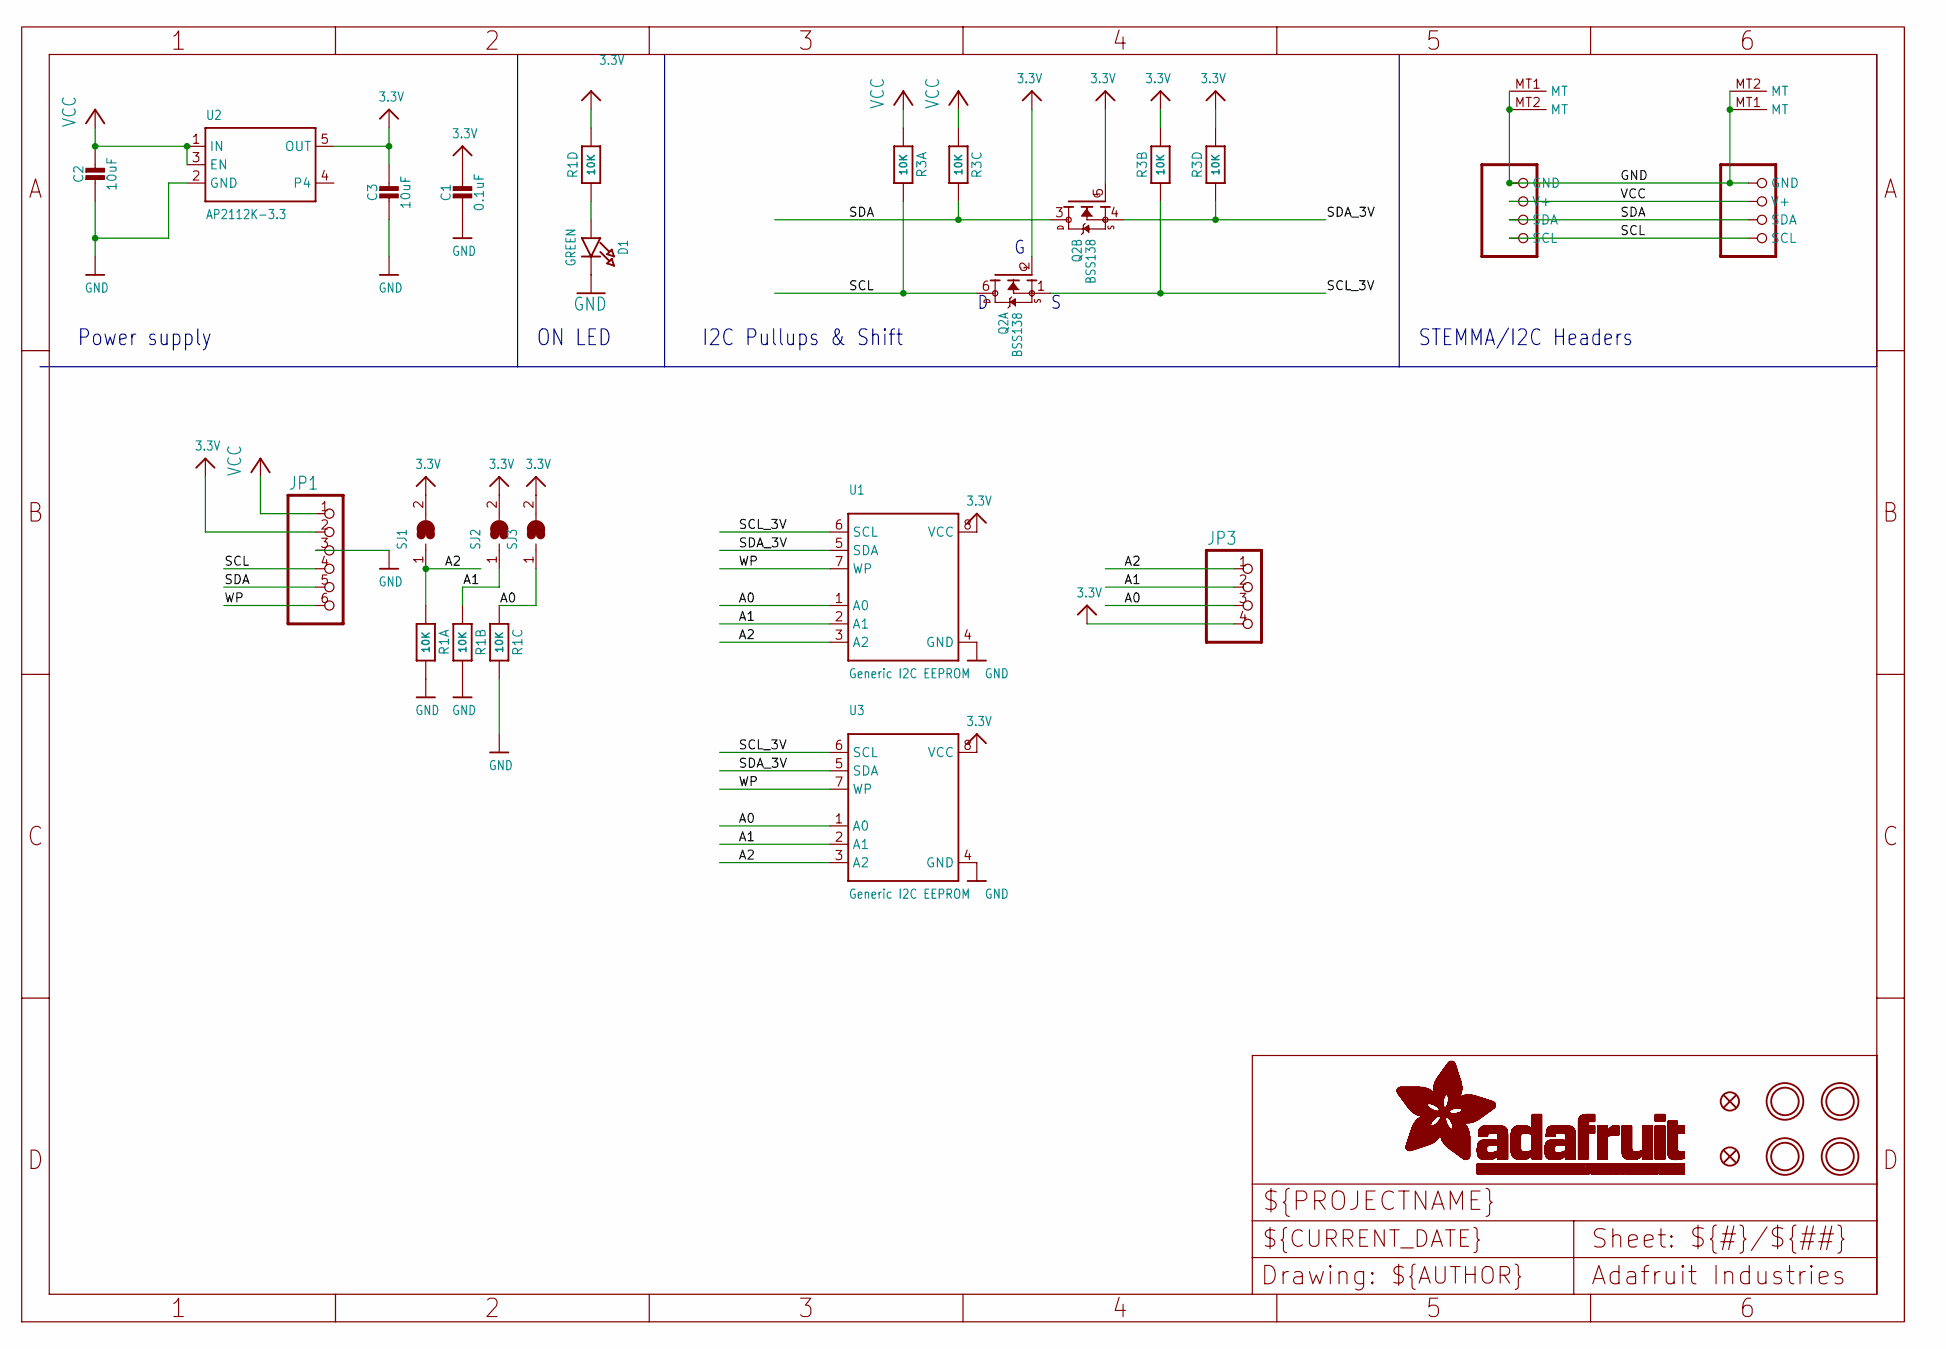
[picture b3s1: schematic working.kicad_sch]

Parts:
C1: 0.1uF; 0603-NO
C2, C3: 10uF; 0805-NO
CONN3, CONN4: STEMMA_I2C_QT; JST_SH4
D1: GREEN; CHIPLED_0603_NOOUTLINE
FID3, FID4: FIDUCIAL_1MM
JP1: HEADER-1X670MIL; 1X06_ROUND_70
JP3: HEADER-1X4ROUND; 1X04_ROUND
Q2: BSS138; SOT363
R1, R3: 10K; RESPACK_4X0603
SJ1, SJ2, SJ3: SOLDERJUMPER; SOLDERJUMPER_ARROW_NOPASTE
U1: Generic I2C EEPROM; SOIC8_150MIL
U2: AP2112K-3.3; SOT23-5
U3: Generic I2C EEPROM; USON8
U$1, U$17, U$19, U$21: MOUNTINGHOLE2.5; MOUNTINGHOLE_2.5_PLATED

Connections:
3.3V: C1.1, C3.1, JP1.2, JP3.4, Q2.2 (G), Q2.5 (G), R1.5 (2), R3.2 (1), R3.4 (1), SJ1.2, SJ2.2, SJ3.2, U1.8 (VCC), U2.5 (OUT), U3.8 (VCC)
A0: JP3.3, R1.3 (1), SJ3.1, U1.1 (A0), U3.1 (A0)
A1: JP3.2, R1.2 (1), SJ2.1, U1.2 (A1), U3.2 (A1)
A2: JP3.1, R1.1, SJ1.1, U1.3 (A2), U3.3 (A2)
GND: C1.2, C2.2, C3.2, CONN3.1 (GND), CONN3.MT1 (MT), CONN3.MT2 (MT), CONN4.1 (GND), CONN4.MT1 (MT), CONN4.MT2 (MT), D1.C, JP1.3, R1.6 (2), R1.7 (2), R1.8 (2), U1.4 (GND), U2.2 (GND), U3.4 (GND)
unnamed: D1.A, R1.4 (1)
SCL: CONN3.4 (SCL), CONN4.4 (SCL), JP1.4, Q2.6 (D), R3.8 (2)
SCL_3V: Q2.1 (S), R3.7 (2), U1.6 (SCL), U3.6 (SCL)
SDA: CONN3.3 (SDA), CONN4.3 (SDA), JP1.5, Q2.3 (D), R3.6 (2)
SDA_3V: Q2.4 (S), R3.5 (2), U1.5 (SDA), U3.5 (SDA)
VCC: C2.1, CONN3.2 (V+), CONN4.2 (V+), JP1.1, R3.1, R3.3 (1), U2.1 (IN), U2.3 (EN)
WP: JP1.6, U1.7 (WP), U3.7 (WP)

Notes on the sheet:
STEMMA/I2C Headers
ON LED
I2C Pullups & Shift
Power supply

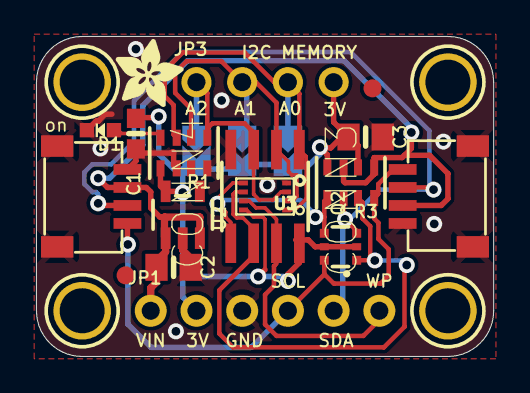
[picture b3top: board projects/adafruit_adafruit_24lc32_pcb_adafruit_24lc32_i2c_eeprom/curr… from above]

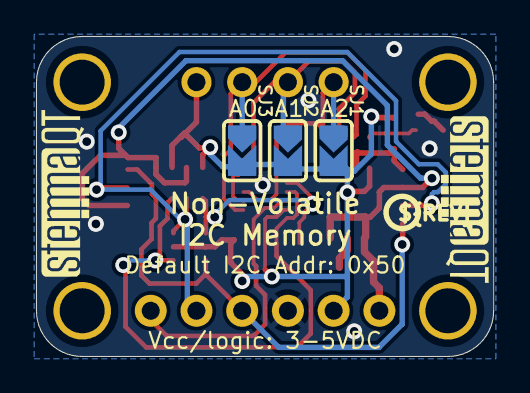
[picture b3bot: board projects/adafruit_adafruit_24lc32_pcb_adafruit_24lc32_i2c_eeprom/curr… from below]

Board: 2 copper layers, 25.4 x 17.8 mm, 27 parts (6 on the bottom side), 12 nets.

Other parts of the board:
U$25: PCBFEAT-REV-040
U$30, U$31: STEMMAQT
U$32: ADAFRUIT_3.5MM

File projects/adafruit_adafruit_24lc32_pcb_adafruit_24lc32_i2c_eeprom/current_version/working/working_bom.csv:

"Id";"Designator";"Footprint";"Quantity";"Designation";"Supplier and ref";
1;"JP3";"1X04_ROUND";1;"";;;
2;"U1";"SOIC8_150MIL";1;"Generic I2C EEPROM";;;
3;"R1,R3";"RESPACK_4X0603";2;"10K";;;
4;"U$32";"ADAFRUIT_3.5MM";1;"";;;
5;"U$17,U$19,U$1,U$21";"MOUNTINGHOLE_2.5_PLATED";4;"MOUNTINGHOLE2.5";;;
6;"Q2";"SOT363";1;"BSS138";;;
7;"C1";"0603-NO";1;"0.1uF";;;
8;"CONN4,CONN3";"JST_SH4";2;"STEMMA_I2C_QT";;;
9;"U3";"USON8";1;"Generic I2C EEPROM";;;
10;"C3,C2";"0805-NO";2;"10uF";;;
11;"JP1";"1X06_ROUND_70";1;"";;;
12;"D1";"CHIPLED_0603_NOOUTLINE";1;"GREEN";;;
13;"U2";"SOT23-5";1;"AP2112K-3.3";;;
14;"FID4,FID3";"FIDUCIAL_1MM";2;"FIDUCIAL_1MM";;;
15;"U$25";"PCBFEAT-REV-040";1;"";;;
16;"U$31,U$30";"STEMMAQT";2;"";;;
17;"SJ2,SJ1,SJ3";"SOLDERJUMPER_ARROW_NOPASTE";3;"";;;
